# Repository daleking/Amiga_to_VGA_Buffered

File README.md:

# Amiga Buffered VGA Adaptor

This VGA buffered adaptor uses a SN74HCT08PWR to keep the size down (and stay true to the original Commodore design).  You will also need a DB23 female solder cup connector and a VGA PCB mount connector (and a capacitor).

This is a replacement for the original [390682-01](http://bboah.amiga-resistance.info/cgi-bin/showhardware_en.cgi?HARDID=733)

I don't know what the other chip in the [390682-03](http://bboah.amiga-resistance.info/download_photos/comm_vgaconv4.jpg) is, or what the diodes (protection?) are for either.  Apparently this version has a fix for video toasters, so assume that this repro will behave the same and not work with video toasters either.

The design is upside down so that there is minimal strain on the DB23 video connector.  The VGA cable lies close to flat on the table.  I didn't want the weight of the cable pulling down on the connector.

No warranty, although I have built one and tested on A4000, A2000 and A500.

This method is a lot easier than stripping wires and soldering the cups :)

If you are lazy, you can order PCBs from [dirtypcbs.com](http://dirtypcbs.com/store/designer/details/dalek/6137/amiga-to-vga-buffered-zip) and using that link I get a dollar woo!  If you are cheap just grab the gerber zip file and get them done wherever you like.

I suggest 1.2mm board thickness (1.6mm works but is a tight fit).

Dale

## Schematic

## Bottom

## Top

## Connected

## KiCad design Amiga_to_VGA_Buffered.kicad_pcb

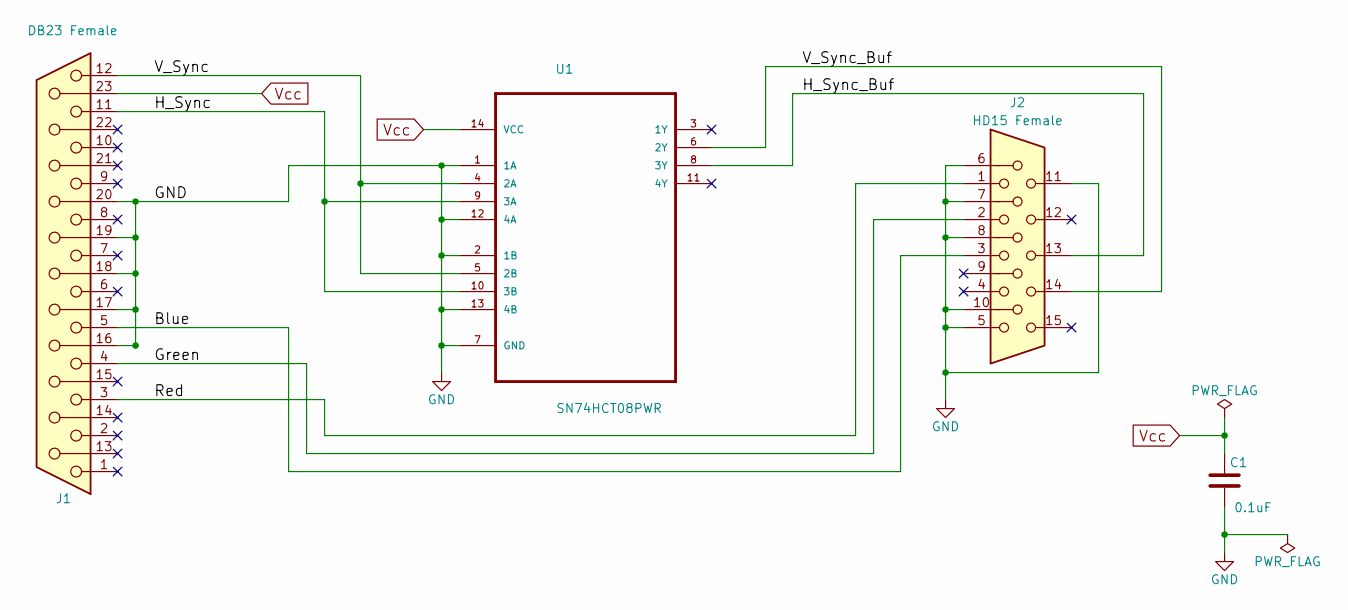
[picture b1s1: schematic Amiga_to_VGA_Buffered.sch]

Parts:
C1: 0.1uF; C_1206
J1: DB23 Female; conn-db23_Female_Solder_Cup
J2: HD15 Female; conn_SPC15430
U1: SN74HCT08PWR; SOP65P640X120-14N

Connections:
/Blue: J1.5, J2.3
/Green: J1.4, J2.2
/H_Sync: J1.11, U1.9 (3A), U1.10 (3B)
/H_Sync_Buf: J2.13, U1.8 (3Y)
/Red: J1.3, J2.1
/V_Sync: J1.12, U1.4 (2A), U1.5 (2B)
/V_Sync_Buf: J2.14, U1.6 (2Y)
GND: C1.2, J1.16, J1.17, J1.18, J1.19, J1.20, J2.5, J2.6, J2.7, J2.8, J2.10, J2.11, U1.1 (1A), U1.2 (1B), U1.7 (GND), U1.12 (4A), U1.13 (4B)
Vcc: C1.1, J1.23, U1.14 (VCC)

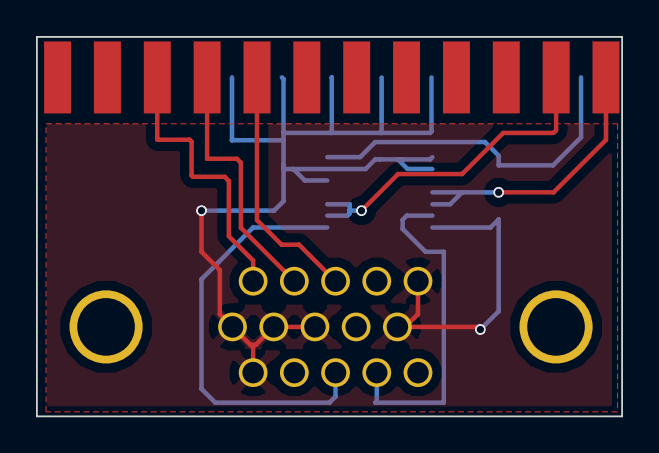
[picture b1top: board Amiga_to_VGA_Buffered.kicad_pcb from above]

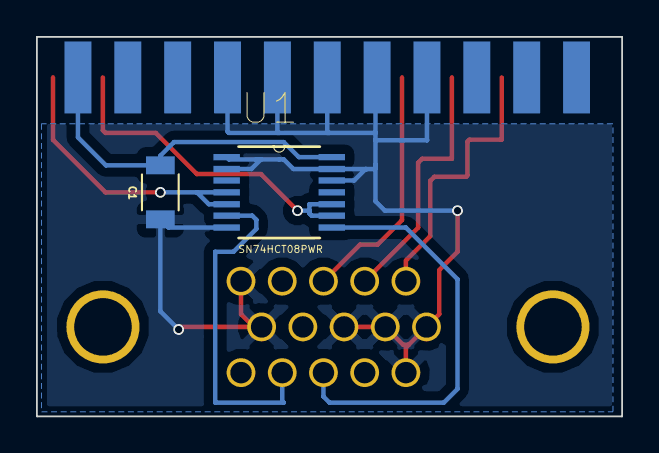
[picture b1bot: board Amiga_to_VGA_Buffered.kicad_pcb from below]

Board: 2 copper layers, 32.5 x 21.1 mm, 4 parts (3 on the bottom side), 9 nets.

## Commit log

2018-09-18 initial
